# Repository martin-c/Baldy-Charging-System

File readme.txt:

Baldy Charging System

An open source Li-Ion BMS and battery charging system.

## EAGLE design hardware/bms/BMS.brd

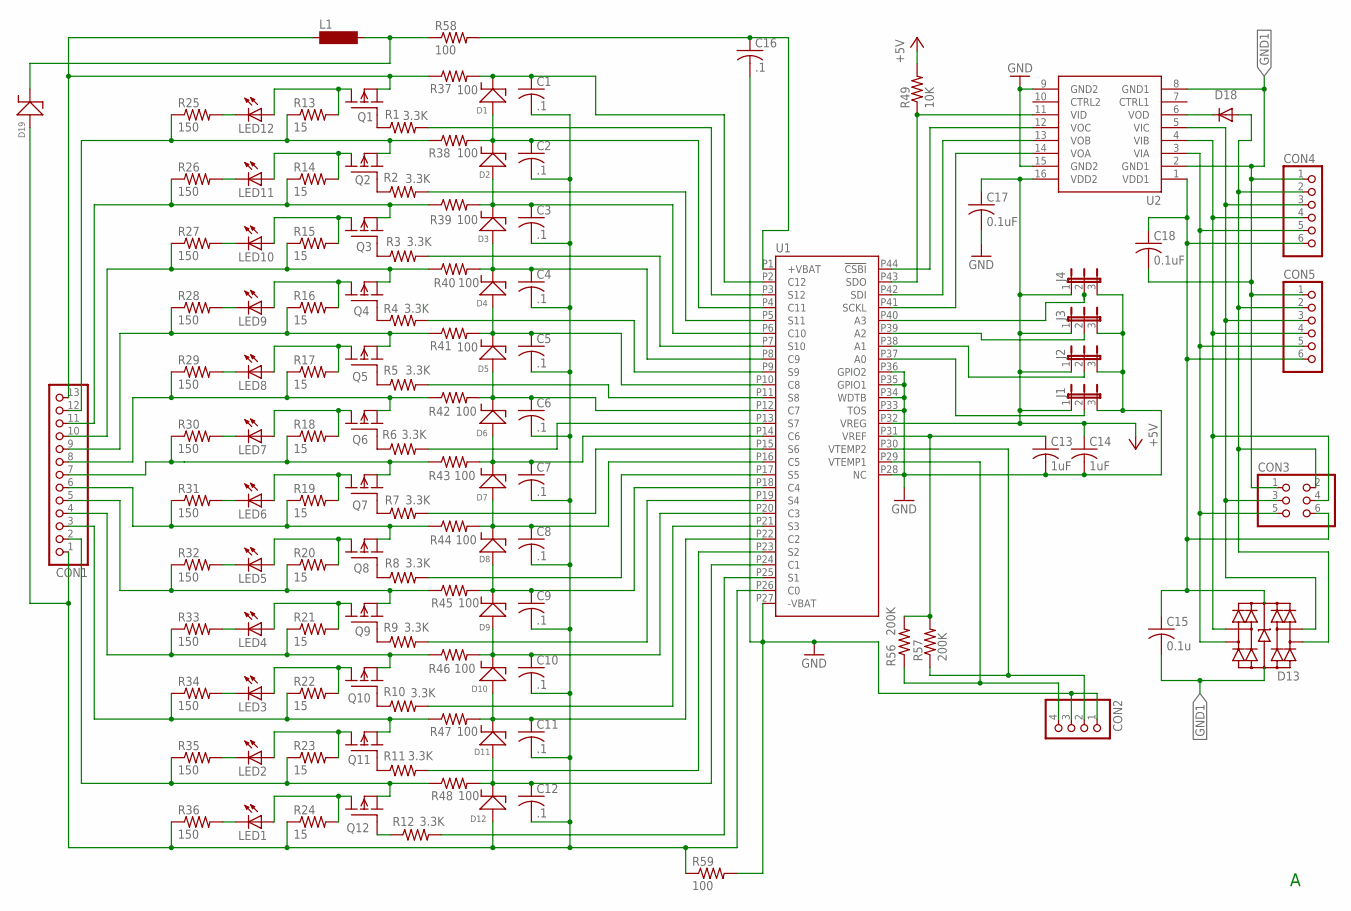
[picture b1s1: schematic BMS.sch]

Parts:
C1, C2, C3, C4, C5, C6, C7, C8, C9, C10, C11, C12, C16: .1; C0603
C13, C14: 1uF; C0603
C15: 0.1u; C0603
C17, C18: 0.1uF; C0603
CON1: PINHD-1X13/90; 1X13/90
CON2: PINHD-1X4/90; 1X04/90
CON3: PINHD-2X3/90; 2X03/90
CON4, CON5: PINHD-1X6/90; 1X06/90
D1, D2, D3, D4, D5, D6, D7, D8, D9, D10, D11, D12: PDZ7.5B; SOD323
D13: TPD4E001DBV; SOT23-6
D18: DIODE0603; LED-0603
D19: MMSZ5265BTIG; SOD-123_MINI-SMA
J1, J2, J3, J4: JP2E; JP2
L1: CHOKE; CHOKE1206
LED1, LED2, LED3, LED4, LED5, LED6, LED7, LED8, LED9, LED10, LED11, LED12: LED0603; LED-0603
Q1, Q2, Q3, Q4, Q5, Q6, Q7, Q8, Q9, Q10, Q11, Q12: FDY102PZ; SC89-3
R1, R2, R3, R4, R5, R6, R7, R8, R9, R10, R11, R12: 3.3K; R0603
R13, R14, R15, R16, R17, R18, R19, R20, R21, R22, R23, R24: 15; R2512
R25, R26, R27, R28, R29, R30, R31, R32, R33, R34, R35, R36: 150; R0603
R37, R38, R39, R40, R41, R42, R43, R44, R45, R46, R47, R48, R58, R59: 100; R0603
R49: 10K; R0603
R56, R57: 200K; R0603
U1: LTC6803-2; SSOP44
U2: ADUM1411RW; SO16W

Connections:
+5V: C14.1, C17.1, J1.1, J2.1, J3.1, J4.1, R49.2, U1.P32 (VREG), U2.16 (VDD2)
+VBAT: C16.1, R58.2, U1.P1 (+VBAT)
GND: C13.2, C14.2, C16.2, C17.2, CON2.1, CON2.3, J1.3, J2.3, J3.3, J4.3, R59.2, U1.P27 (-VBAT), U1.P28 (NC), U1.P33 (TOS), U1.P34 (WDTB), U1.P35 (GPIO1), U1.P36 (GPIO2), U2.9 (GND2), U2.15 (GND2)
GND1: C15.2, C18.2, CON3.1, CON4.1, CON5.1, D13.2 (GND), U2.2 (GND1), U2.8 (GND1)
unnamed: C8.1, D7.P$2 (2), D8.P$1 (1), R44.2, U1.P16 (C5)
unnamed: CON1.2, Q12.P$2 (S), R23.1, R35.1, R48.1
unnamed: C2.1, D1.P$2 (2), D2.P$1 (1), R38.2, U1.P4 (C11)
unnamed: C3.1, D2.P$2 (2), D3.P$1 (1), R39.2, U1.P6 (C10)
unnamed: C4.1, D3.P$2 (2), D4.P$1 (1), R40.2, U1.P8 (C9)
unnamed: C5.1, D4.P$2 (2), D5.P$1 (1), R41.2, U1.P10 (C8)
unnamed: C6.1, D5.P$2 (2), D6.P$1 (1), R42.2, U1.P12 (C7)
unnamed: C7.1, D6.P$2 (2), D7.P$1 (1), R43.2, U1.P14 (C6)
unnamed: C10.1, D9.P$2 (2), D10.P$1 (1), R46.2, U1.P20 (C3)
unnamed: C11.1, D10.P$2 (2), D11.P$1 (1), R47.2, U1.P22 (C2)
unnamed: C12.1, D11.P$2 (2), D12.P$1 (1), R48.2, U1.P24 (C1)
unnamed: C1.2, C2.2, C3.2, C4.2, C5.2, C6.2, C7.2, C8.2, C9.2, C10.2, C11.2, C12.2, CON1.1, D12.P$2 (2), D19.A (2), R24.1, R36.1, R59.1, U1.P26 (C0)
unnamed: Q1.P$1 (G), R1.1
unnamed: Q2.P$1 (G), R2.1
unnamed: Q3.P$1 (G), R3.1
unnamed: Q4.P$1 (G), R4.1
unnamed: Q5.P$1 (G), R5.1
unnamed: Q6.P$1 (G), R6.1
unnamed: Q7.P$1 (G), R7.1
unnamed: Q8.P$1 (G), R8.1
unnamed: Q9.P$1 (G), R9.1
unnamed: Q10.P$1 (G), R10.1
unnamed: Q11.P$1 (G), R11.1
unnamed: J3.2, U1.P39 (A2)
unnamed: LED12.A, Q1.P$3 (D), R13.2
unnamed: LED12.C, R25.2
unnamed: R1.2, U1.P3 (S12)
unnamed: LED11.A, Q2.P$3 (D), R14.2
unnamed: LED11.C, R26.2
unnamed: LED10.C, R27.2
unnamed: CON1.10, Q4.P$2 (S), R15.1, R27.1, R40.1
unnamed: LED10.A, Q3.P$3 (D), R15.2
unnamed: R2.2, U1.P5 (S11)
unnamed: R3.2, U1.P7 (S10)
unnamed: R4.2, U1.P9 (S9)
unnamed: R5.2, U1.P11 (S8)
unnamed: R6.2, U1.P13 (S7)
unnamed: R7.2, U1.P15 (S6)
unnamed: R8.2, U1.P17 (S5)
unnamed: R9.2, U1.P19 (S4)
unnamed: R10.2, U1.P21 (S3)
unnamed: R11.2, U1.P23 (S2)
unnamed: R12.2, U1.P25 (S1)
unnamed: J1.2, U1.P37 (A0)
unnamed: CON1.13, L1.1, Q1.P$2 (S), R37.1
unnamed: LED7.C, R30.2
unnamed: LED9.A, Q4.P$3 (D), R16.2
unnamed: LED9.C, R28.2
unnamed: LED8.A, Q5.P$3 (D), R17.2
unnamed: LED7.A, Q6.P$3 (D), R18.2
unnamed: LED8.C, R29.2
unnamed: CON1.12, Q2.P$2 (S), R13.1, R25.1, R38.1
unnamed: LED6.C, R31.2
unnamed: LED6.A, Q7.P$3 (D), R19.2
unnamed: CON1.11, Q3.P$2 (S), R14.1, R26.1, R39.1
unnamed: CON3.2, CON4.2, CON5.2, D13.6 (IO4), D18.A
unnamed: LED5.A, Q8.P$3 (D), R20.2
unnamed: LED5.C, R32.2
unnamed: LED4.C, R33.2
unnamed: LED3.C, R34.2
unnamed: LED4.A, Q9.P$3 (D), R21.2
unnamed: LED3.A, Q10.P$3 (D), R22.2
unnamed: LED2.C, R35.2
unnamed: LED1.A, Q12.P$3 (D), R24.2
unnamed: LED2.A, Q11.P$3 (D), R23.2
unnamed: CON1.9, Q5.P$2 (S), R16.1, R28.1, R41.1
unnamed: CON1.8, Q6.P$2 (S), R17.1, R29.1, R42.1
unnamed: CON1.7, Q7.P$2 (S), R18.1, R30.1, R43.1
unnamed: CON1.6, Q8.P$2 (S), R19.1, R31.1, R44.1
unnamed: CON1.5, Q9.P$2 (S), R20.1, R32.1, R45.1
unnamed: CON1.4, Q10.P$2 (S), R21.1, R33.1, R46.1
unnamed: CON1.3, Q11.P$2 (S), R22.1, R34.1, R47.1
unnamed: U1.P44 (!CSBI), U2.12 (VOC)
unnamed: R49.1, U1.P43 (SDO), U2.11 (VID)
unnamed: U1.P42 (SDI), U2.13 (VOB)
unnamed: U1.P41 (SCKL), U2.14 (VOA)
unnamed: CON3.5, CON4.5, CON5.5, D13.1 (IO1), U2.3 (VIA)
unnamed: J2.2, U1.P38 (A1)
unnamed: CON3.4, CON4.4, CON5.4, D13.3 (IO2), U2.4 (VIB)
unnamed: CON3.3, CON4.3, CON5.3, D13.4 (IO3), U2.5 (VIC)
unnamed: D18.C, U2.6 (VOD)
unnamed: J4.2, U1.P40 (A3)
unnamed: CON2.4, R56.1, U1.P29 (VTEMP1)
unnamed: CON2.2, R57.1, U1.P30 (VTEMP2)
unnamed: C1.1, D1.P$1 (1), R37.2, U1.P2 (C12)
unnamed: D19.C (1), L1.2, R58.1
unnamed: LED1.C, R36.2
unnamed: Q12.P$1 (G), R12.1
unnamed: C9.1, D8.P$2 (2), D9.P$1 (1), R45.2, U1.P18 (C4)
VDD1: C15.1, C18.1, CON3.6, CON4.6, CON5.6, D13.5 (VCC), U2.1 (VDD1)
VREF: C13.1, R56.2, R57.2, U1.P31 (VREF)

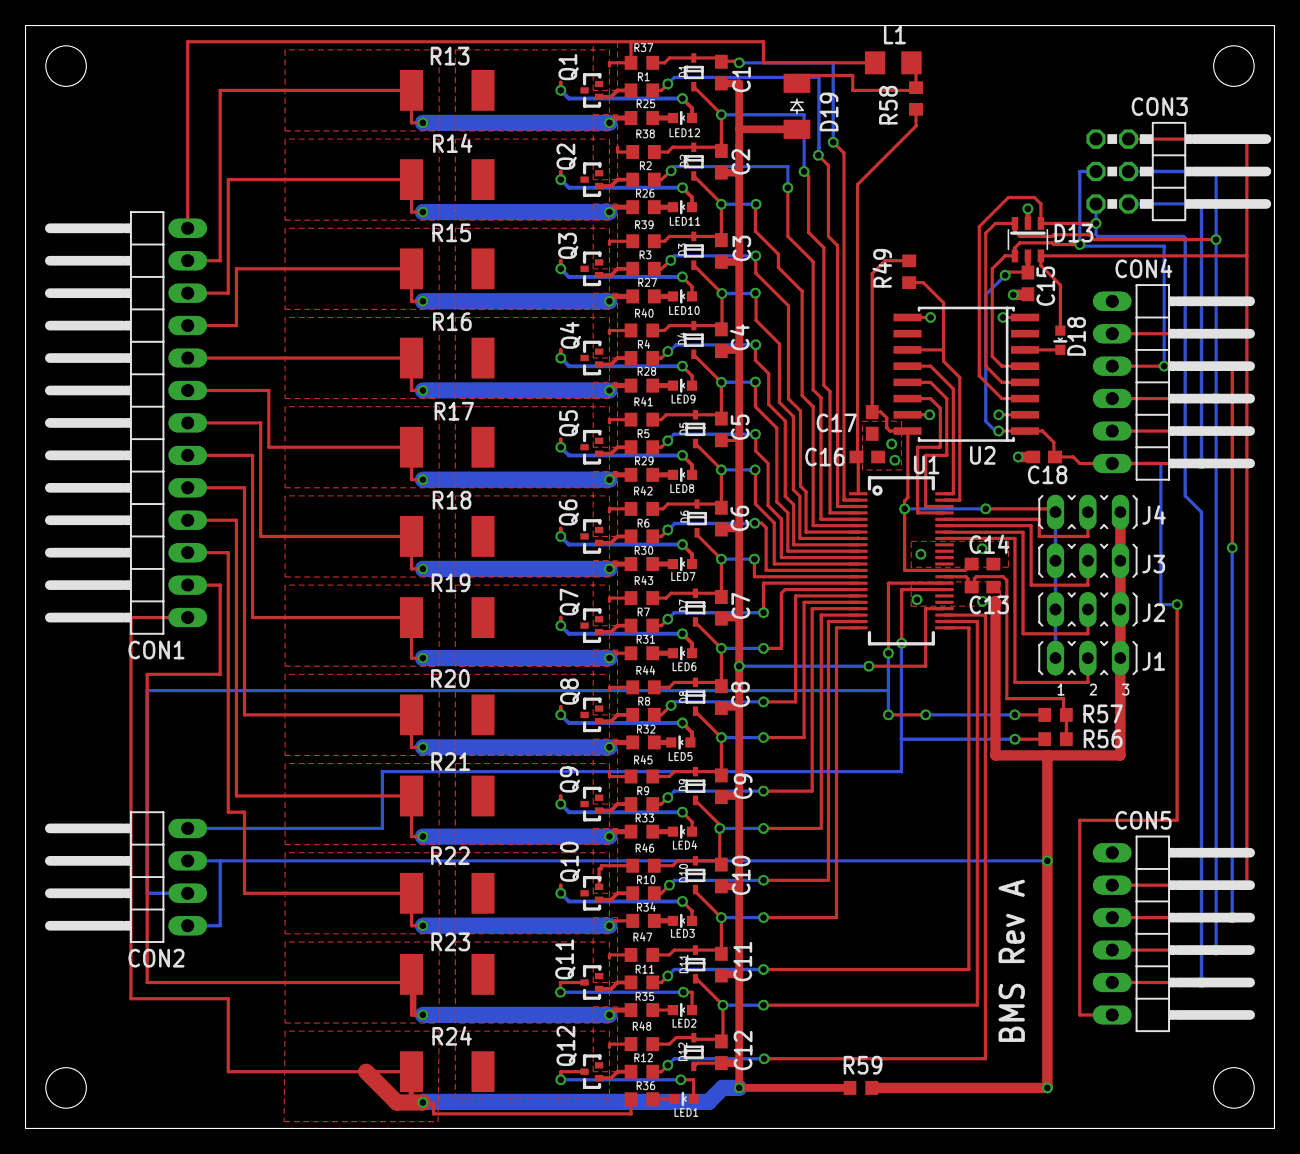
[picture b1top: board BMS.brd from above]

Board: 2 copper layers, 97.8 x 86.4 mm, 122 parts (0 on the bottom side), 95 nets.

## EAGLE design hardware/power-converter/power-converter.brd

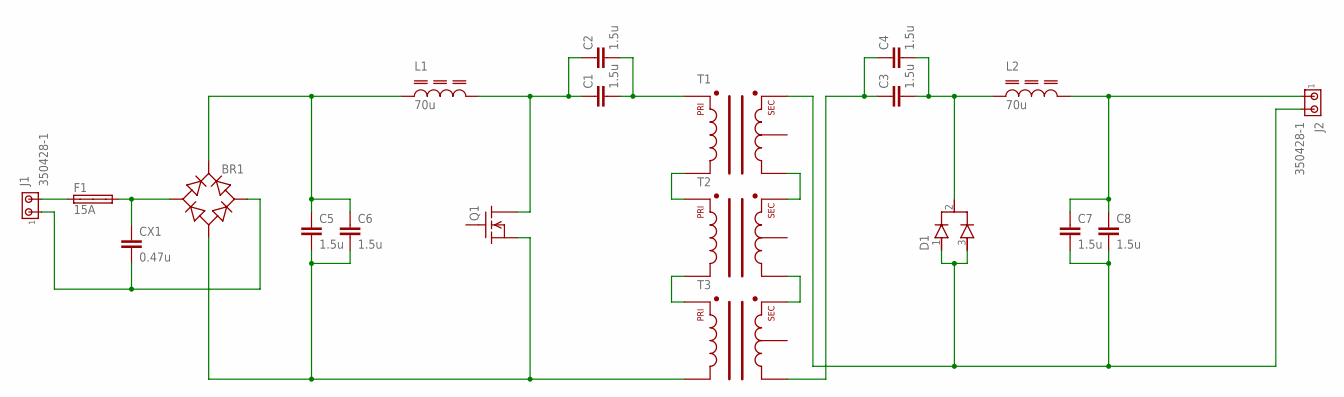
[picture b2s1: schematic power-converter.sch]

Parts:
BR1: DIODE_BRIDGE_RECTIFIERLVB2560; GSIB-5S
C1, C2, C3, C4, C5, C6, C7, C8: 1.5u; PANASONIC-ECWF-2155-B
CX1: 0.47u; XC22B7; PARTNUM PHE840MY6470MD14R06L2
D1: DIODE-COMMON_CATHODETO-247; TO247BV; PARTNUM C3D20060D
F1: 15A; SH32
J1, J2: 350428-1
L1, L2: 70u; COIL-WINDING-SPECIALIST_E70340-016
Q1: N-MOS(G,D,S)TO-220A; TO220AV; PARTNUM STP57N65M5
T1, T2, T3: PAYTON_755001

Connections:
unnamed: BR1.AC1, CX1.1, F1.2A
unnamed: BR1.AC2, CX1.2, J1.1
unnamed: F1.1A, J1.2
unnamed: BR1.NEG, C5.2, C6.2, Q1.3 (S), T3.8,9 (PRI_UNDOT)
unnamed: T2.8,9 (PRI_UNDOT), T3.1,2 (PRI_DOT)
unnamed: T1.8,9 (PRI_UNDOT), T2.1,2 (PRI_DOT)
unnamed: T2.16,17,18 (SEC_UNDOT), T3.10,11,12 (SEC_DOT)
unnamed: T1.16,17,18 (SEC_UNDOT), T2.10,11,12 (SEC_DOT)
unnamed: C3.1, C4.1, T3.16,17,18 (SEC_UNDOT)
unnamed: C3.2, C4.2, D1.2 (CATHODE), L2.1_B, L2.1_T
unnamed: BR1.POS, C5.1, C6.1, L1.1_B, L1.1_T
unnamed: C7.2, C8.2, D1.1 (ANODE), D1.3 (ANODE), J2.2, T1.10,11,12 (SEC_DOT)
unnamed: C7.1, C8.1, J2.1, L2.2_B, L2.2_T
unnamed: C1.1, C2.1, L1.2_B, L1.2_T, Q1.2 (D)
unnamed: C1.2, C2.2, T1.1,2 (PRI_DOT)

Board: 2 copper layers, 20 parts (2 on the bottom side), 15 nets, no tracks yet.

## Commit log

2013-02-16 First completed version of the BMS board schematic and layout for Martin to check and comment on. By Richard Weaver 2/16/13
2013-02-16 Not using Richard.lbr anymore.
2013-04-05 Add initial version of power converter schematic and board.
2013-04-06 Add 2013-04-05 test CAM job.
2013-04-06 Update ground planes, fix misc. route alignment, add decoupling capacitor for '1411. Add ESD protection diode array.
2013-04-08 BMS board SPI protected by a diode array in a single package and package labels adjusted to not touch tstop areas.
2013-04-08 A couple of minor reroute changes to the layout
2013-04-08 I added the documentation to github
2013-04-09 Minor change to schematic
2013-04-10 Move ESD suppression diode array between inputs and level shift IC. Add decoupling capacitor on level shift IC.
2013-05-18 Create "design docs" subfolder, move design documents into new folder.
2013-05-18 Add initial files for master-control schematic.
2013-05-18 Ignore eagle backup files.
2013-05-28 Add user-interface hardware project eagle files.
2013-05-28 Add data sheets folder. Make changes to master-control to eliminate LCD and keypad, begin adding isoSPI ICs.
2013-05-28 Add Honeywell hall-effect current sensor datasheet.
2013-05-28 Add LTC 6804 datasheet.
2013-11-23 Initial commit of hello world code.
2014-01-09 Add LTC 6804 libraries to bms dev project. Begin porting source to AVR.
2014-01-09 update intiger types and clean up function names.
2014-01-09 Initial version of basic ‘6804 data reading.
2014-03-26 New BMS layout and schematic
    bmsE.pcb and bmsE.sch are the new ExpressPCB files. The Gerber
    subdirectory contains the manufacturing files.
2014-06-07 New extended 6" board with 5W resistors.
    Still needs the transistor pad sizes reduced. Decided not to add a
    jumper for pull down resistor for current measurement sensor. Instead
    this resistor will be external to the board. It will work with the DHAB
    S/14. Did not change pad size on 0603. Large through hole fuse, zener
    and schottky diode for protection.
2014-06-25 Updated BMS board layout and uP control board doc
2014-06-26 Updated master control board specification
2014-06-26 Updated BMS design specification
2014-06-26 Shortened BMS layout by .05" to fit in case
2014-08-23 Added 4 temp sensing diodes
2014-08-30 Updated parts list for 4 temp sensor diodes
2014-12-29 Add zip archive with Gerber files for BMS board PCB production.
